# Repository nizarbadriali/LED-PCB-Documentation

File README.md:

# LED PCB — Simple 5V Circuit with Custom SPICE Model

**Status:** Schematic and PCB designed; LTspice simulation completed; uploaded ERC, DRC, and schematic-parity results show zero reported violations under the configured checks. Manufacturing files exported. Physical assembly and testing pending.

## What This Is

A simple 5V → 220 Ω resistor → red LED → ground circuit, developed to practice circuit calculations, SPICE model fitting, PCB layout, and fabrication-file verification. The diode model is fitted to supplied I–V data whose provenance is not yet documented. Simulation results are predictions, not physical measurements.

## Results

| Parameter | Value | Evidence or qualification |
|-----------|-------|---------------------------|
| Predicted LED current | 14.3515 mA | Saved LTspice operating point |
| Predicted LED voltage | 1.84267 V | Saved LTspice operating point |
| Resistor dissipation | 45.31 mW | Calculated from simulated current using I²R |
| Routed trace width | 0.4 mm (15.75 mil) | PCB source file |
| Copper thickness | 35 µm per side (approximately 1 oz) | Intended fabrication specification in Gerber job file |
| Board dimensions / thickness | 100 × 60 mm / 1.6 mm | PCB outline and board settings |
| ERC / DRC | Zero reported errors and warnings | Uploaded check screenshots; configured exclusions discussed in design notes |
| Schematic-to-PCB parity | Zero differences | Uploaded parity-check screenshot |
| Manufacturing package | Gerbers and Excellon drills | [gerbers.zip](kicad/gerbers.zip) |

## Quick Start

**View the design:** Open [Simple LED.kicad_pro](kicad/Simple%20LED.kicad_pro) in KiCad 9, then open the schematic and PCB from the project manager.

**Run the simulation:** Open [led_circuit.asc](simulation/ltspice/led_circuit.asc) in LTspice and run its `.op` analysis. The complete `led_red` model directive is embedded in that file. See the [saved simulation log](simulation/ltspice/led_circuit.log).

**Run the model fitter:** From the repository root, with NumPy and SciPy installed:

```bash
python3 -m pip install numpy scipy
python3 simulation/python/led_model.py
```

The script prints model directives; it does not write `.lib` files. Changing the reference models in `models/` does not automatically update the model embedded in LTspice.

## Bill of Materials

| Reference | Value | Package / specification | Selection status |
|-----------|-------|-------------------------|------------------|
| R2 | 220 Ω, ¼ W | Axial; footprint `R_Axial_DIN0207_L6.3mm_D2.5mm_P7.62mm_Horizontal` | Select part with compatible body, lead diameter, and bent lead spacing; part number and tolerance pending |
| D1 | Red LED | 5 mm through-hole; 2.54 mm pin spacing | Part number, polarity drawing, and electrical ratings pending |
| J1 | 2-pin header | 2.54 mm pitch; pin 1 = +5V, pin 2 = GND | Manufacturer part number pending |

The resistor is R1 in LTspice and R2 in KiCad. The model identifier is `led_red`; the reference library filename is `red_led.lib`.

## Project Files

| Path | Contents |
|------|----------|
| `kicad/` | Project, schematic, PCB, screenshots, and manufacturing ZIP |
| `simulation/ltspice/` | Circuit with embedded model and operating-point log |
| `simulation/python/led_model.py` | Model fitter |
| `simulation/matlab/led_model.m` | Educational implementation with known limitations |
| `models/` | Reference red and blue model directives |
| `workdir/` | Supplied two-column I–V data at repository root |
| [DESIGN_NOTES.md](DESIGN_NOTES.md) | Design decisions, actual revisions, checks, and fabrication details |
| [SPICE_MODELING.md](SPICE_MODELING.md) | Data, fitting method, fit errors, and model limitations |

## Limitations and Next Steps

- Document the data source, LED identity, measurement method, and temperature. The supplied red-LED point of 0.5 V at 1 mA particularly needs verification.
- Select actual component part numbers and check their datasheets against the footprints and operating conditions.
- Assemble and test the board; measure LED voltage and infer current from the voltage across the measured resistor resistance.
- Compare bench results with predictions before claiming physical validation.

## Tools and Attribution

- KiCad 9.0.7: source/export metadata.
- LTspice 17.2.4: saved simulation log.
- Python fitter independently exercised during documentation review with Python 3.12.14, NumPy 2.3.5, and SciPy 1.17.0. These are review-environment versions, not a claim about the original development environment or all supported versions.

Model-fitting methodology is based on [Ted Yapo's LED modeling project](https://github.com/tedyapo/led-modeling). See [SPICE_MODELING.md](SPICE_MODELING.md) for details and references.

## License

MIT License. See [LICENSE](LICENSE).

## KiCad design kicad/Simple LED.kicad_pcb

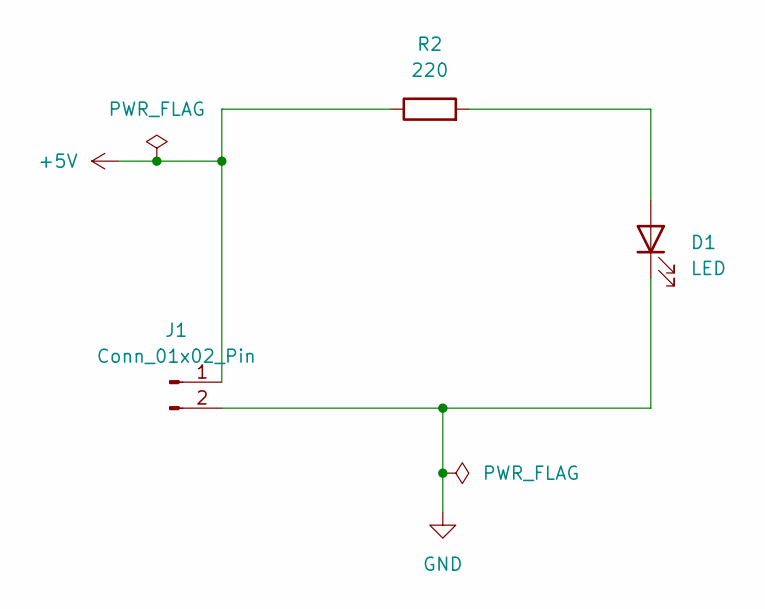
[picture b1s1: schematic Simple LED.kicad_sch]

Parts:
D1: LED; LED_D5.0mm
J1: Conn_01x02_Pin; PinHeader_1x02_P2.54mm_Vertical
R2: 220; R_Axial_DIN0207_L6.3mm_D2.5mm_P7.62mm_Horizontal

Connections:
+5V: J1.1, R2.1
GND: D1.1 (K), J1.2
unnamed: D1.2 (A), R2.2

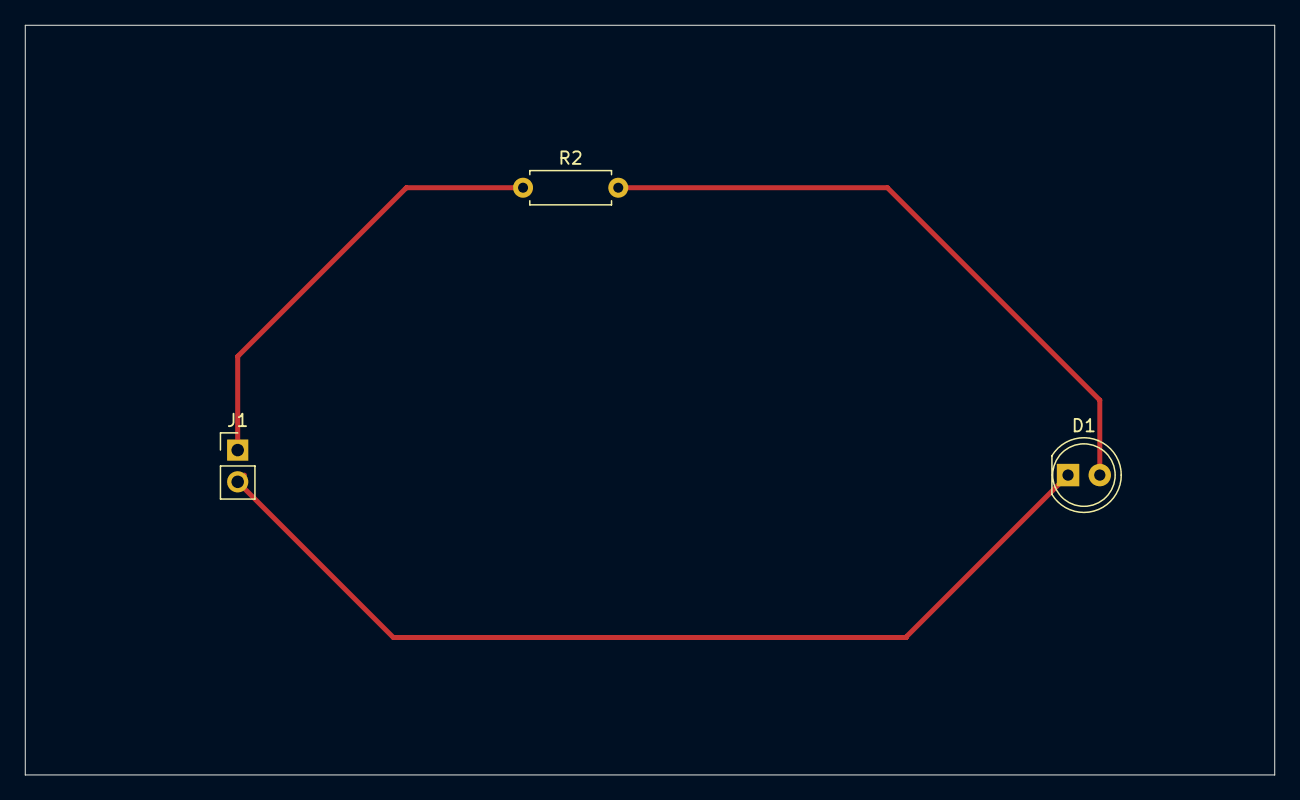
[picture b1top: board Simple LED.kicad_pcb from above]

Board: 2 copper layers, 100.0 x 60.0 mm, 3 parts (0 on the bottom side), 3 nets.
